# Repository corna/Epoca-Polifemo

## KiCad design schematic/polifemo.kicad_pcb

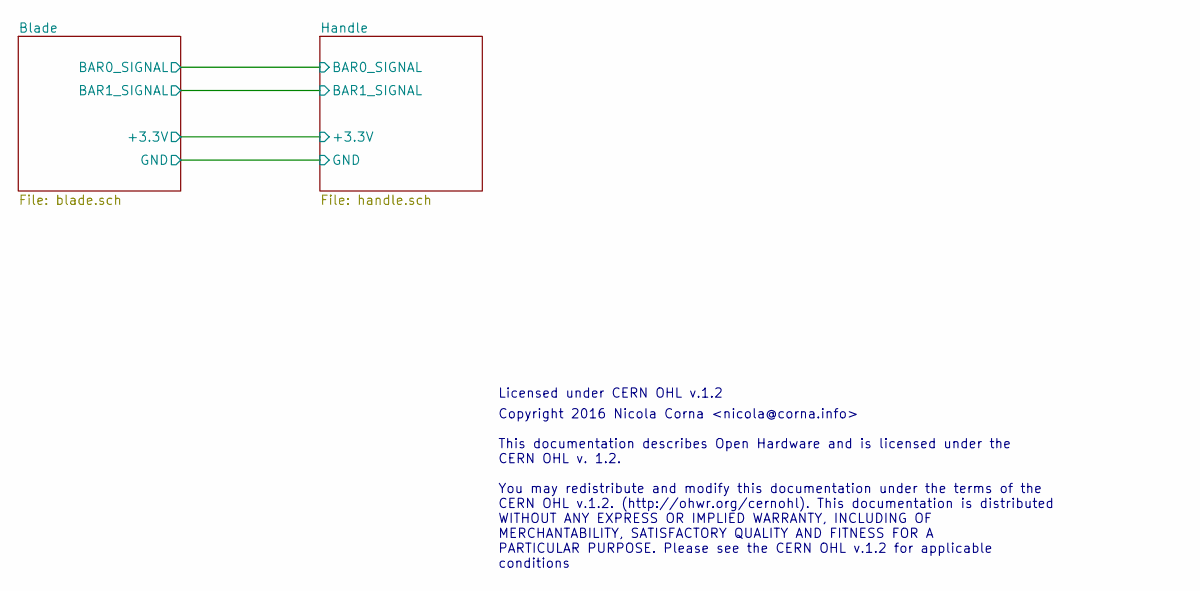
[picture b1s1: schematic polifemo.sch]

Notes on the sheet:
Copyright 2016 Nicola Corna <nicola@corna.info> This documentation describes Open Hardware and is licensed under the CERN OHL v. 1.2. You may redistribute and modify this documentation under the terms of the CERN OHL v.1.2. (http://ohwr.org/cernohl). This documentation is distributed WITHOUT ANY EX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
Licensed under CERN OHL v.1.2

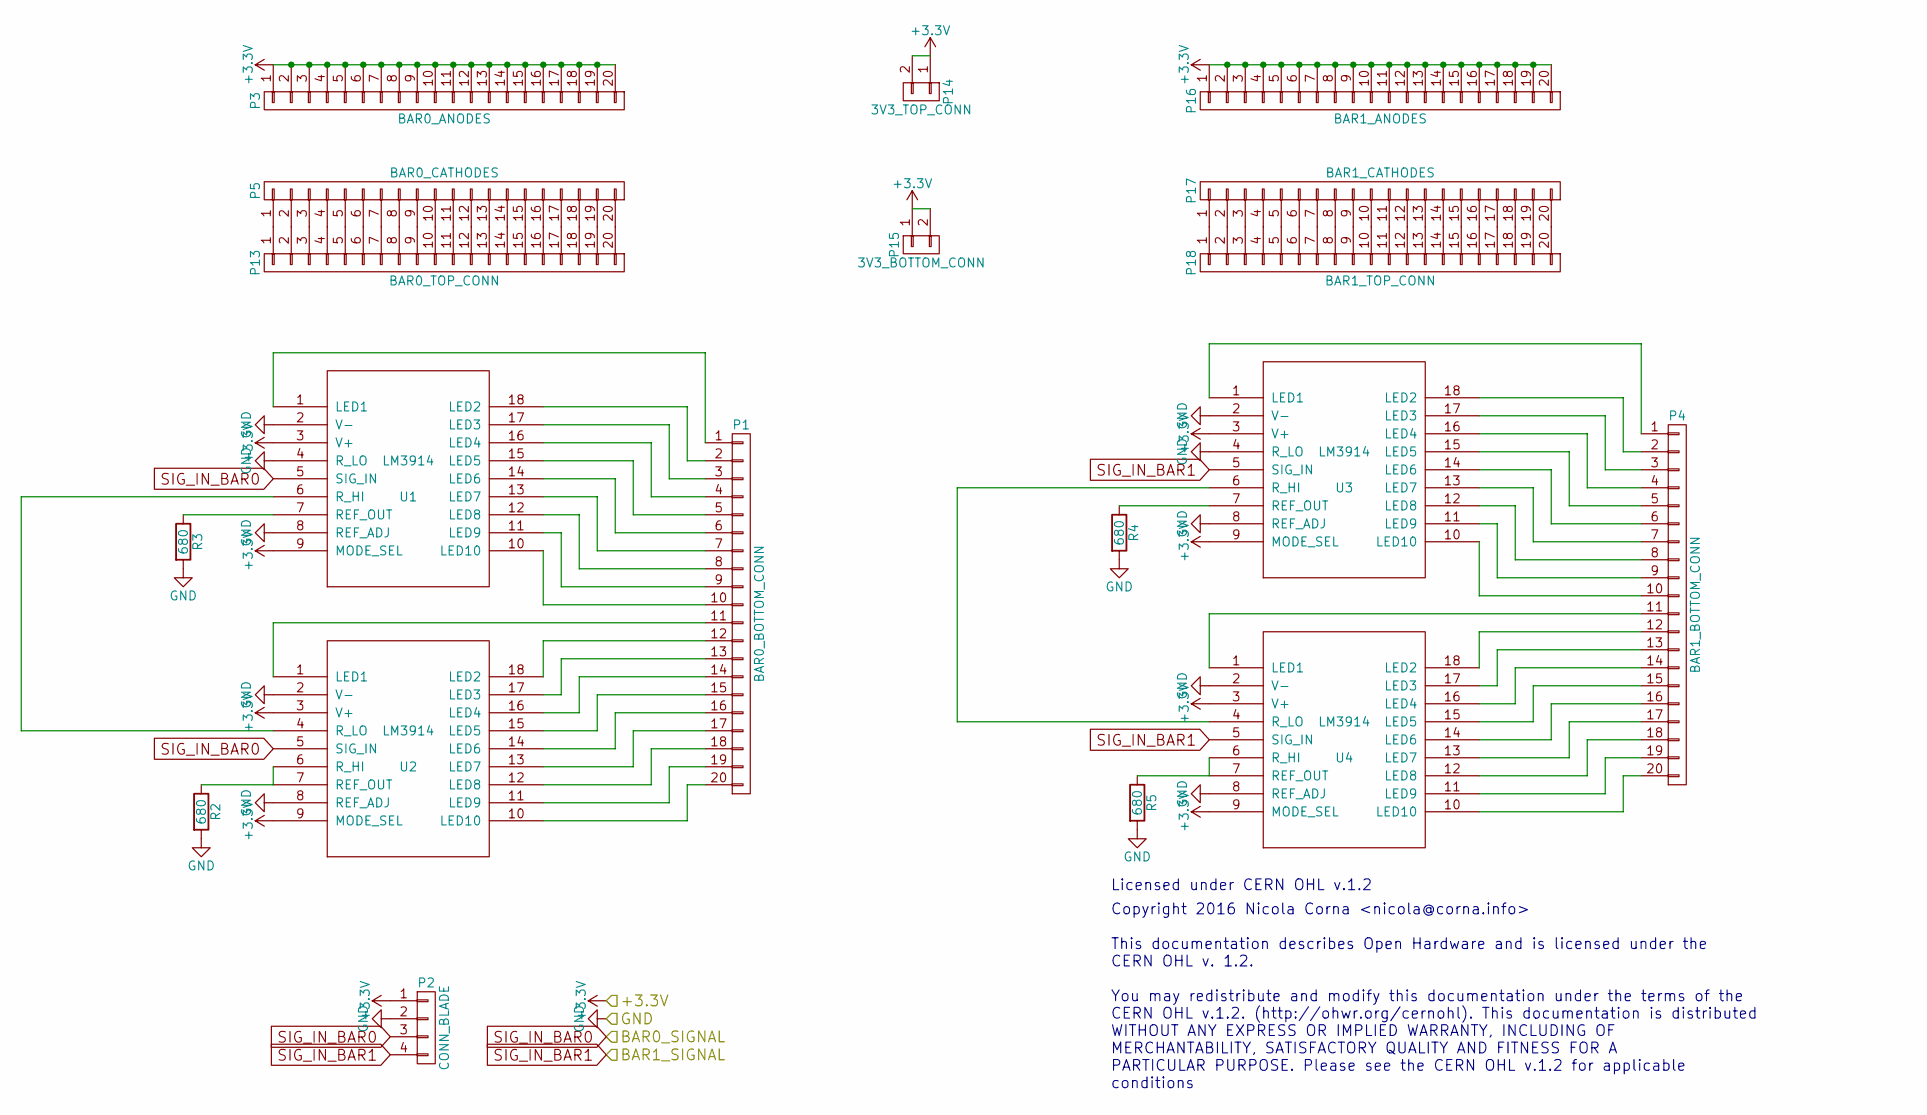
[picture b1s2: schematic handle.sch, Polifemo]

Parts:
P1: BAR0_BOTTOM_CONN; Pin_Header_Straight_1x20
P2: CONN_BLADE; Socket_Strip_Straight_1x04
P3: BAR0_ANODES; Socket_Strip_Straight_1x20
P4: BAR1_BOTTOM_CONN; Pin_Header_Straight_1x20
P5: BAR0_CATHODES; Socket_Strip_Straight_1x20
P13: BAR0_TOP_CONN; Socket_Strip_Straight_1x20
P14: 3V3_TOP_CONN; Socket_Strip_Straight_1x02
P15: 3V3_BOTTOM_CONN; Pin_Header_Straight_1x02
P16: BAR1_ANODES; Socket_Strip_Straight_1x20
P17: BAR1_CATHODES; Socket_Strip_Straight_1x20
P18: BAR1_TOP_CONN; Socket_Strip_Straight_1x20
R2, R3, R4, R5: 680; R_1206
U1, U2, U3, U4: LM3914; DIP-18_W7.62mm

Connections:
+3V3: P2.1, P3.1, P3.2, P3.3, P3.4, P3.5, P3.6, P3.7, P3.8, P3.9, P3.10, P3.11, P3.12, P3.13, P3.14, P3.15, P3.16, P3.17, P3.18, P3.19, P3.20, P14.1, P14.2, P15.1, P15.2, P16.1, P16.2, P16.3, P16.4, P16.5, P16.6, P16.7, P16.8, P16.9, P16.10, P16.11, P16.12, P16.13, P16.14, P16.15, P16.16, P16.17, P16.18, P16.19, P16.20, U1.3 (V+), U1.9 (MODE_SEL), U2.3 (V+), U2.9 (MODE_SEL), U3.3 (V+), U3.9 (MODE_SEL), U4.3 (V+), U4.9 (MODE_SEL); also elsewhere on the board
GND: P2.2, R2.2, R3.2, R4.2, R5.2, U1.2 (V-), U1.4 (R_LO), U1.8 (REF_ADJ), U2.2 (V-), U2.8 (REF_ADJ), U3.2 (V-), U3.4 (R_LO), U3.8 (REF_ADJ), U4.2 (V-), U4.8 (REF_ADJ); also elsewhere on the board
unnamed: P1.1, U1.1 (LED1)
unnamed: P1.2, U1.18 (LED2)
unnamed: P1.3, U1.17 (LED3)
unnamed: P1.4, U1.16 (LED4)
unnamed: P1.5, U1.15 (LED5)
unnamed: P1.6, U1.14 (LED6)
unnamed: P1.7, U1.13 (LED7)
unnamed: P1.8, U1.12 (LED8)
unnamed: P1.9, U1.11 (LED9)
unnamed: P1.10, U1.10 (LED10)
unnamed: P1.11, U2.1 (LED1)
unnamed: P1.12, U2.18 (LED2)
unnamed: P1.13, U2.17 (LED3)
unnamed: P1.14, U2.16 (LED4)
unnamed: P1.15, U2.15 (LED5)
unnamed: P1.16, U2.14 (LED6)
unnamed: P1.17, U2.13 (LED7)
unnamed: P1.18, U2.12 (LED8)
unnamed: P1.19, U2.11 (LED9)
unnamed: P1.20, U2.10 (LED10)
unnamed: P4.1, U3.1 (LED1)
unnamed: P4.2, U3.18 (LED2)
unnamed: P4.3, U3.17 (LED3)
unnamed: P4.4, U3.16 (LED4)
unnamed: P4.5, U3.15 (LED5)
unnamed: P4.6, U3.14 (LED6)
unnamed: P4.7, U3.13 (LED7)
unnamed: P4.8, U3.12 (LED8)
unnamed: P4.9, U3.11 (LED9)
unnamed: P4.10, U3.10 (LED10)
unnamed: P4.11, U4.1 (LED1)
unnamed: P4.12, U4.18 (LED2)
unnamed: P4.13, U4.17 (LED3)
unnamed: P4.14, U4.16 (LED4)
unnamed: P4.15, U4.15 (LED5)
unnamed: P4.16, U4.14 (LED6)
unnamed: P4.17, U4.13 (LED7)
unnamed: P4.18, U4.12 (LED8)
unnamed: P4.19, U4.11 (LED9)
unnamed: P4.20, U4.10 (LED10)
unnamed: P5.1, P13.1
unnamed: P5.2, P13.2
unnamed: P5.3, P13.3
unnamed: P5.4, P13.4
unnamed: P5.5, P13.5
unnamed: P5.6, P13.6
unnamed: P5.7, P13.7
unnamed: P5.8, P13.8
unnamed: P5.9, P13.9
unnamed: P5.10, P13.10
unnamed: P5.11, P13.11
unnamed: P5.12, P13.12
unnamed: P5.13, P13.13
unnamed: P5.14, P13.14
unnamed: P5.15, P13.15
unnamed: P5.16, P13.16
unnamed: P5.17, P13.17
unnamed: P5.18, P13.18
unnamed: P5.19, P13.19
unnamed: P5.20, P13.20
unnamed: P17.1, P18.1
unnamed: P17.2, P18.2
unnamed: P17.3, P18.3
unnamed: P17.4, P18.4
unnamed: P17.5, P18.5
unnamed: P17.6, P18.6
unnamed: P17.7, P18.7
unnamed: P17.8, P18.8
unnamed: P17.9, P18.9
unnamed: P17.10, P18.10
unnamed: P17.11, P18.11
unnamed: P17.12, P18.12
unnamed: P17.13, P18.13
unnamed: P17.14, P18.14
unnamed: P17.15, P18.15
unnamed: P17.16, P18.16
unnamed: P17.17, P18.17
unnamed: P17.18, P18.18
unnamed: P17.19, P18.19
unnamed: P17.20, P18.20
unnamed: R2.1, U2.6 (R_HI), U2.7 (REF_OUT)
unnamed: R3.1, U1.7 (REF_OUT)
unnamed: R4.1, U3.7 (REF_OUT)
unnamed: R5.1, U4.6 (R_HI), U4.7 (REF_OUT)
unnamed: U1.6 (R_HI), U2.4 (R_LO)
unnamed: U3.6 (R_HI), U4.4 (R_LO)
SIG_IN_BAR0: P2.3, U1.5 (SIG_IN), U2.5 (SIG_IN); also elsewhere on the board
SIG_IN_BAR1: P2.4, U3.5 (SIG_IN), U4.5 (SIG_IN); also elsewhere on the board

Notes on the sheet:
Copyright 2016 Nicola Corna <nicola@corna.info> This documentation describes Open Hardware and is licensed under the CERN OHL v. 1.2. You may redistribute and modify this documentation under the terms of the CERN OHL v.1.2. (http://ohwr.org/cernohl). This documentation is distributed WITHOUT ANY EX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
Licensed under CERN OHL v.1.2

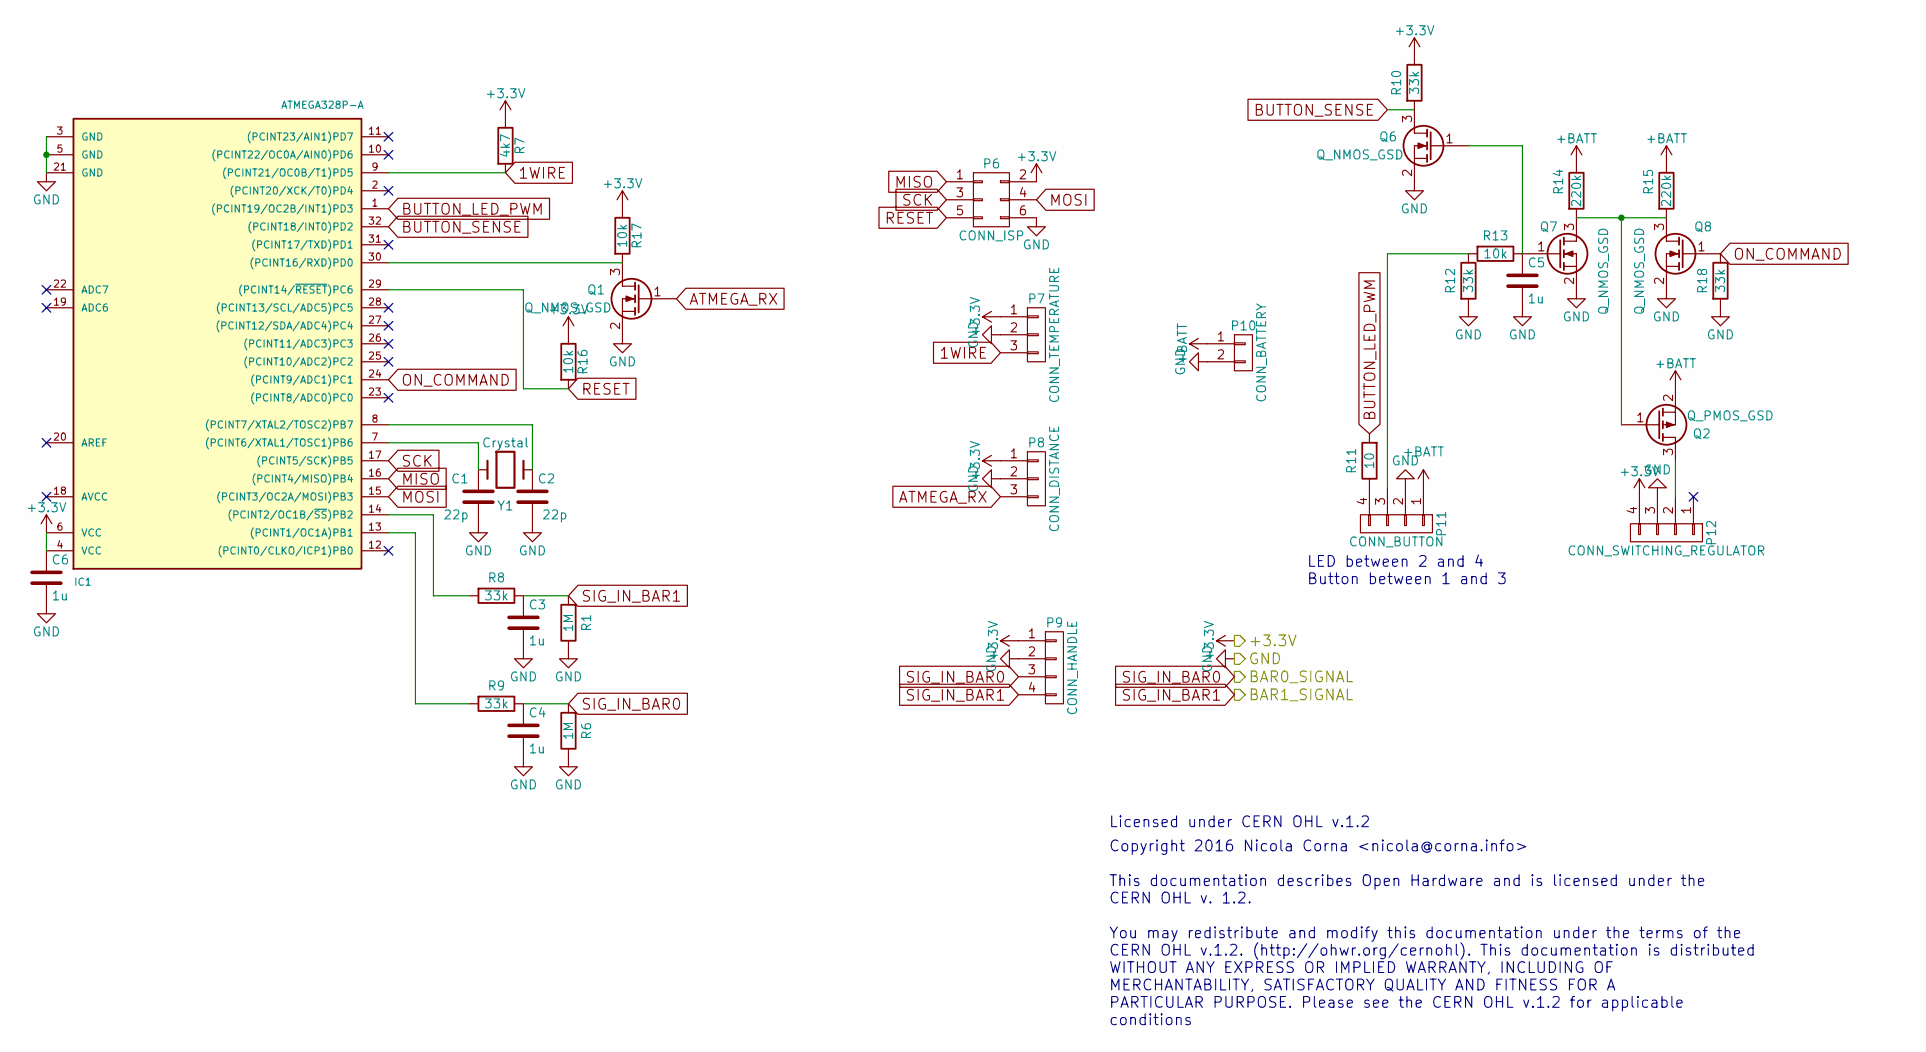
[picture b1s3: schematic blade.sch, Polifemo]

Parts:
C1, C2: 22p; C_1206
C3, C4, C5, C6: 1u; C_1206
IC1: ATMEGA328P-A; TQFP-32_7x7mm_Pitch0.8mm
P6: CONN_ISP; Pin_Header_Straight_2x03
P7: CONN_TEMPERATURE; Pin_Header_Straight_1x03
P8: CONN_DISTANCE; Pin_Header_Straight_1x03
P9: CONN_HANDLE; Socket_Strip_Straight_1x04
P10: CONN_BATTERY; Pin_Header_Straight_1x02
P11: CONN_BUTTON; Pin_Header_Straight_1x04
P12: CONN_SWITCHING_REGULATOR; Pin_Header_Straight_1x04
Q1, Q6, Q7, Q8: Q_NMOS_GSD; SOT-23
Q2: Q_PMOS_GSD; SOT-23
R1, R6: 1M; R_1206
R7: 4k7; R_1206
R8, R9, R10, R12, R18: 33k; R_1206
R11: 10; R_1206
R13, R16, R17: 10k; R_1206
R14, R15: 220k; R_1206
Y1: Crystal; Crystal_HC49-SD_SMD

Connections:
1WIRE: IC1.9 ((PCINT21/OC0B/T1)PD5), P7.3, R7.2
+3V3: C6.1, IC1.4 (VCC), IC1.6 (VCC), P6.2, P7.1, P8.1, P9.1, P12.4, R7.1, R10.1, R16.1, R17.1; also elsewhere on the board
+BATT: P10.1, P11.1, Q2.2 (S), R14.1, R15.1
ATMEGA_RX: P8.3, Q1.1 (G)
BUTTON_LED_PWM: IC1.1 ((PCINT19/OC2B/INT1)PD3), R11.2
BUTTON_SENSE: IC1.32 ((PCINT18/INT0)PD2), Q6.3 (D), R10.2
GND: C1.1, C2.2, C3.2, C4.2, C5.2, C6.2, IC1.3 (GND), IC1.5 (GND), IC1.21 (GND), P6.6, P7.2, P8.2, P9.2, P10.2, P11.2, P12.3, Q1.2 (S), Q6.2 (S), Q7.2 (S), Q8.2 (S), R1.1, R6.1, R12.2, R18.2; also elsewhere on the board
MISO: IC1.16 ((PCINT4/MISO)PB4), P6.1
MOSI: IC1.15 ((PCINT3/OC2A/MOSI)PB3), P6.4
unnamed: C1.2, IC1.7 ((PCINT6/XTAL1/TOSC1)PB6), Y1.1
unnamed: C2.1, IC1.8 ((PCINT7/XTAL2/TOSC2)PB7), Y1.2
unnamed: C5.1, Q6.1 (G), Q7.1 (G), R13.1
unnamed: IC1.13 ((PCINT1/OC1A)PB1), R9.2
unnamed: IC1.14 ((PCINT2/OC1B/~SS~)PB2), R8.2
unnamed: IC1.30 ((PCINT16/RXD)PD0), Q1.3 (D), R17.2
unnamed: P11.3, R12.1, R13.2
unnamed: P11.4, R11.1
unnamed: P12.2, Q2.3 (D)
unnamed: Q2.1 (G), Q7.3 (D), Q8.3 (D), R14.2, R15.2
ON_COMMAND: IC1.24 ((PCINT9/ADC1)PC1), Q8.1 (G), R18.1
RESET: IC1.29 ((PCINT14/~RESET~)PC6), P6.5, R16.2
SCK: IC1.17 ((PCINT5/SCK)PB5), P6.3
SIG_IN_BAR0: C4.1, P9.3, R6.2, R9.1; also elsewhere on the board
SIG_IN_BAR1: C3.1, P9.4, R1.2, R8.1; also elsewhere on the board

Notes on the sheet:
LED between 2 and 4 Button between 1 and 3
Copyright 2016 Nicola Corna <nicola@corna.info> This documentation describes Open Hardware and is licensed under the CERN OHL v. 1.2. You may redistribute and modify this documentation under the terms of the CERN OHL v.1.2. (http://ohwr.org/cernohl). This documentation is distributed WITHOUT ANY EX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
Licensed under CERN OHL v.1.2

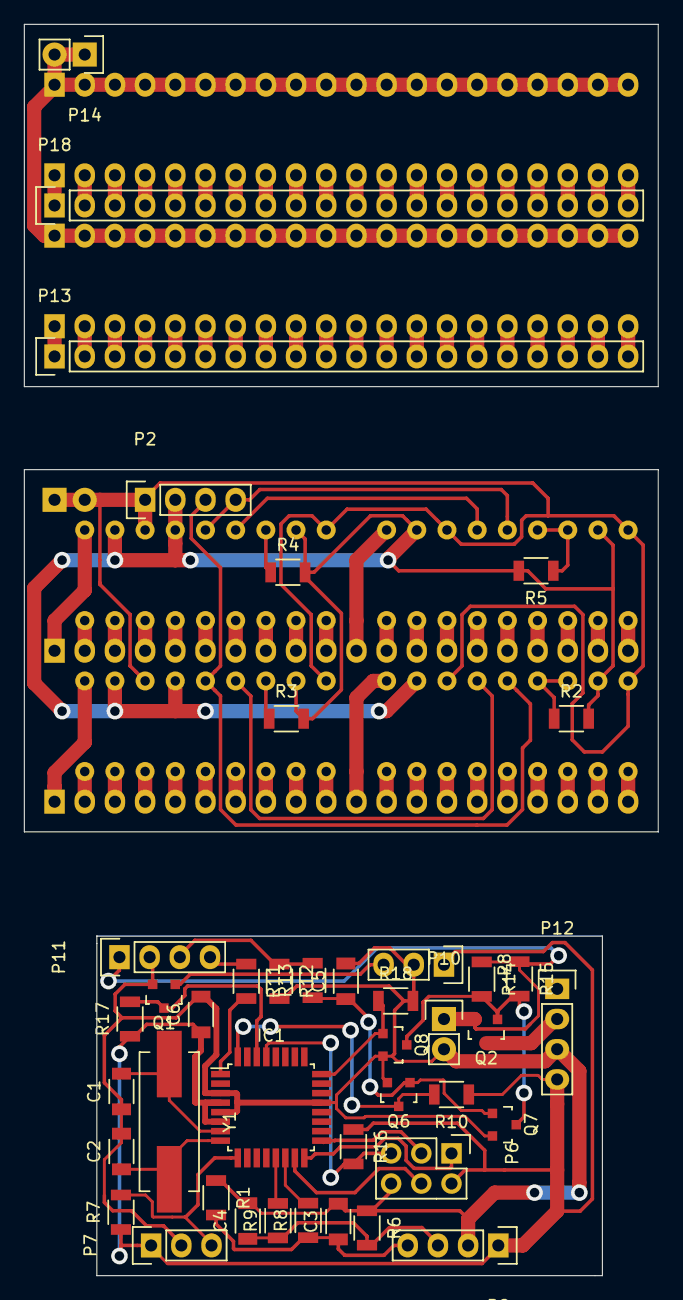
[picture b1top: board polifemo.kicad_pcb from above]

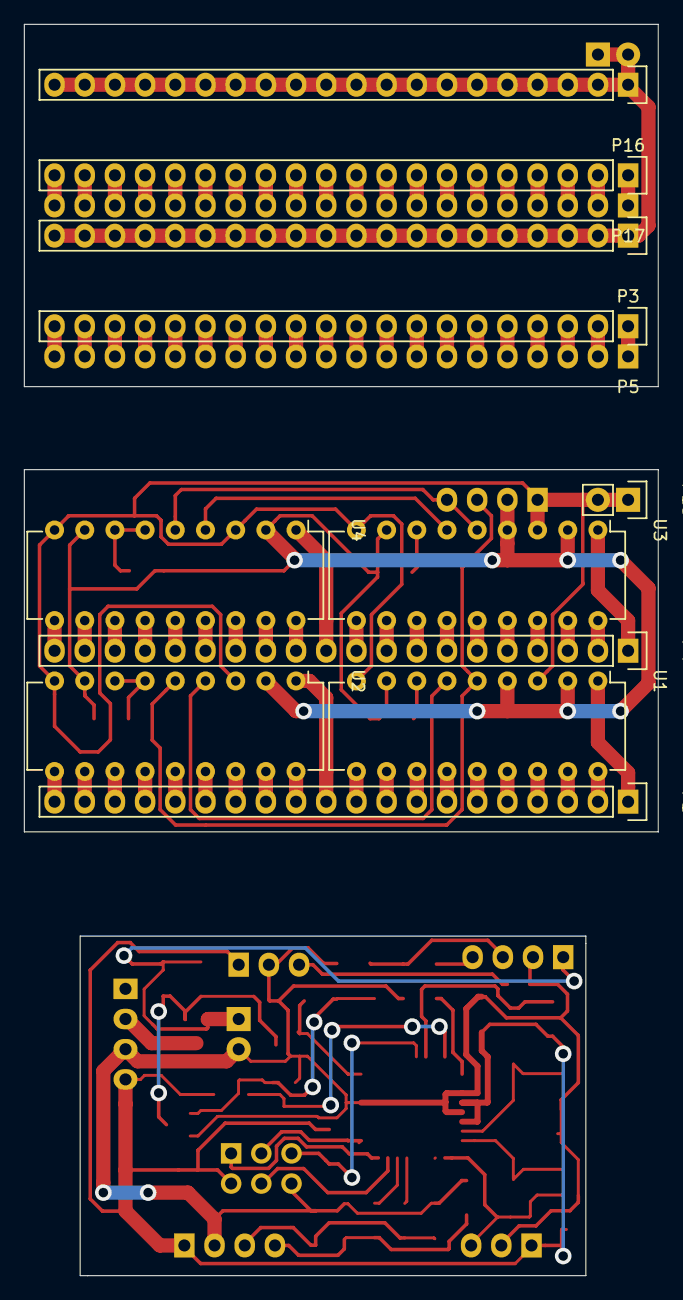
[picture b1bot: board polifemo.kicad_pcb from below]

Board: 2 copper layers, 53.3 x 105.3 mm, 53 parts (11 on the bottom side), 110 nets.

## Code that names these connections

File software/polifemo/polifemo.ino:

/*
 * Epoca Polifemo
 * Copyright (C) 2016 Nicola Corna <nicola@corna.info>
 *
 * This program is free software: you can redistribute it and/or modify
 * it under the terms of the GNU General Public License as published by
 * the Free Software Foundation, either version 3 of the License, or
 * (at your option) any later version.
 *
 * This program is distributed in the hope that it will be useful,
 * but WITHOUT ANY WARRANTY; without even the implied warranty of
 * MERCHANTABILITY or FITNESS FOR A PARTICULAR PURPOSE.  See the
 * GNU General Public License for more details.
 *
 * You should have received a copy of the GNU General Public License
 * along with this program.  If not, see <http://www.gnu.org/licenses/>.
 *
 */

#include <avr/sfr_defs.h>
#include <avr/wdt.h>
#include <stdint.h>

#include <TaskScheduler.h>
#include <OneWire.h>
#include <DallasTemperature.h>

#include "MedianFilter.h"
#include "MovingAverage.h"

const uint8_t onCommand = A1;   // PC1 (A1 = 15)
const uint8_t buttonLedPWM = 3; // PD3, OC2B
const uint8_t buttonSense = 2;  // PD2, INT0
const uint8_t sigBar0 = 9;      // PB1, OC1A
const uint8_t sigBar1 = 10;     // PB2, OC1B
const uint8_t ds18b20 = 5;      // PD5 (OC0B)

const unsigned long totalTime = 20000;
const uint16_t refreshPeriod = 120;

const uint8_t watchDogTimeout = WDTO_500MS; //Make sure that watchDogTimeout >> refreshPeriod

const uint16_t dimUpPeriod = 5;
const uint8_t dimUpStep = 2;    //The total dimUp time is dimUpPeriod * (255 / dimUpStep)

const uint16_t dimDownPeriod = 10;
const uint8_t dimDownStep = 2;  //The total dimDown time is dimDownPeriod * (255 / dimDownStep)

/*
const uint16_t distanceMin = 20;
const uint16_t distanceMax = 765;
*/

//30 cm per step
const uint16_t distanceMin = 20;
const uint16_t distanceMax = 600;

//2 °C per step
const int16_t temperatureMin = -3 * 128;
const int16_t temperatureMax = 35 * 128;

//The maximum input value for the LED bars is 1.25V: we have to scale the maximum PWM in order to match it
const uint8_t sigBarMaxPWM = 115;

int16_t ledBrightness = 0;
bool buttonPressed = false;

OneWire oneWire(ds18b20);
DallasTemperature temperatureBus(&oneWire);
DeviceAddress temperatureAddress;

int16_t temperature = 20 * 128;  // 1/128 °C
uint16_t distance = 20;   // cm

MedianFilter<uint16_t, 3> distanceMedian(0xFFFF, distance);
MovingAverage<uint16_t, 5> distanceAverage(distance);

String rawRx = "";

//Forward declarations
void powerButtonPressed();
void displayData();
void updateAndDisplayData();
void dimUp();
void dimDown();
void powerOffSequence();

Task updateAndDisplayDataTask(refreshPeriod, TASK_FOREVER, &updateAndDisplayData);
Task dimUpTask(dimUpPeriod, TASK_FOREVER, &dimUp);
Task dimDownTask(dimDownPeriod, TASK_FOREVER, &dimDown);
Task powerOffSequenceTask(totalTime, TASK_ONCE, &powerOffSequence);

Scheduler runner;

//Disable the watchdog as soon as possible (we don't want the watchdog during the initialization phase)
//see http://www.nongnu.org/avr-libc/user-manual/group__avr__watchdog.html
void get_mcusr(void) __attribute__((naked)) __attribute__((section(".init3")));
void get_mcusr(void)
{
  MCUSR = 0;
  wdt_disable();
}

void setup() {
  //Set the direction and the default value of all the pins
  pinMode(onCommand, OUTPUT);
  digitalWrite(onCommand, HIGH);

  pinMode(buttonLedPWM, OUTPUT);
  analogWrite(buttonLedPWM, ledBrightness);

  pinMode(buttonSense, INPUT);
  //Not optimal: if the user keeps the button pressed the interrupt is fired only once (but who cares??)
  attachInterrupt(digitalPinToInterrupt(buttonSense), powerButtonPressed, CHANGE);

  pinMode(sigBar0, OUTPUT);
  pinMode(sigBar1, OUTPUT);

  displayData();

  //We're throwing the sigBarN outputs in a 1st order LPF, therefore the higher the frequency of the PWM, the more stable the response
  //Here's we're setting the prescaler equal to 1 and the Fast-PWM mode (PWM frequency = 43.2 kHz)
  //This interferes with the Servo library
  TCCR1B |= _BV(CS10) | _BV(WGM12);
  TCCR1B &= ~( _BV(CS11) | _BV(CS12) );

  Serial.begin(9600);

  temperatureBus.begin();
  if (temperatureBus.getAddress(temperatureAddress, 0))
  {
    temperatureBus.setWaitForConversion(false);
    temperatureBus.setResolution(9);
    temperatureBus.requestTemperatures();
  }

  pinMode(LED_BUILTIN, OUTPUT);
  delay(100); //Now both the measurements should be ready

  runner.addTask(updateAndDisplayDataTask);
  runner.addTask(dimUpTask);
  runner.addTask(dimDownTask);
  runner.addTask(powerOffSequenceTask);

  updateAndDisplayDataTask.enableDelayed();
  dimUpTask.enableDelayed();
  powerOffSequenceTask.enableDelayed();
  
  wdt_reset();
  wdt_enable(watchDogTimeout);  //Enable the watchdog; see dimDown
}

void loop() {
  runner.execute();

  if (buttonPressed) {
    buttonPressed = false;
    powerOffSequenceTask.restartDelayed();  //Restart the poweroff timer
    dimDownTask.disable();                  //Remove an eventual dimDown
  
    if (ledBrightness != 255)
      dimUpTask.enableDelayed();  //Increase the LED's brightness if they're not at 100%
    }
}

void powerButtonPressed() {
  buttonPressed = true;
}

void updateAndDisplayData() {
  static String rawRx;
  int8_t start;
  int8_t end;
  char buffer[65];
  int16_t rawTemperature;
  
  wdt_reset();

  //Temperature
  rawTemperature = temperatureBus.getTemp(temperatureAddress);
  if (rawTemperature > DEVICE_DISCONNECTED_RAW)
    temperature = constrain(rawTemperature, temperatureMin, temperatureMax);

  temperatureBus.requestTemperaturesByAddress(temperatureAddress);
  
  //Distance
  end = Serial.available();
  Serial.readBytes(buffer, end);
  buffer[end] = '\0';

  rawRx += buffer;
  end = rawRx.lastIndexOf('\r');
  
  if (end > 0) {
    start = rawRx.lastIndexOf('R', end);

    if (start >= 0) {
      uint16_t unfilteredDistance = rawRx.substring(start + 1, end).toInt();
      
      if (unfilteredDistance != 0) {
        distance = distanceAverage.filter(distanceMedian.filter(constrain(unfilteredDistance, distanceMin, distanceMax)));
      }
      
      rawRx.remove(0, end + 1); //Throw away older data
    }
  }

  displayData();

  wdt_reset();
}

void displayData() {
  static const uint8_t sigBarStep = sigBarMaxPWM / 19;
  static const uint8_t sigBarStep_2 = sigBarStep / 2;

  uint8_t value;

  //Find the maximum PWM value, a combination of ledBrightness (0->255) and sigBarMaxPWM(0->255)
  //For an explaination of that "+ 1" see this link http://forum.arduino.cc/index.php/topic,46546.0.html
  const uint8_t maxPWM = map(ledBrightness, 0, 255 + 1, 0, sigBarMaxPWM + 1);

  //Then map the distance (distanceMin->distanceMax) to the new PWM range(0->maxPWM)
  value = map(distance, distanceMin, distanceMax + 1, 0, maxPWM + 1);

  //Then approximate the final value to one of the 20 steps
  value = (value + sigBarStep_2) / sigBarStep * sigBarStep;
  analogWrite(sigBar1, value);

  value =  map(temperature, temperatureMin, temperatureMax + 1, 0, maxPWM + 1);
  value = (value + sigBarStep_2) / sigBarStep * sigBarStep;
  analogWrite(sigBar0, value);
}

void dimUp() {
  ledBrightness = constrain(ledBrightness + dimUpStep, 0, 255);
  analogWrite(buttonLedPWM, ledBrightness);
  displayData();

  if (ledBrightness == 255) //Maximum brightness reached
    dimUpTask.disable();
}

void dimDown() {
  ledBrightness = constrain(ledBrightness - dimDownStep, 0, 255);
  analogWrite(buttonLedPWM, ledBrightness);
  displayData();

  if (ledBrightness == 0) { //Minimum brightness reached
    digitalWrite(onCommand, LOW); //Power off everything

    wdt_reset();
    while(true) {    
      //Force a watchdog timeout if the AVR is still on after watchDogTimeout
      //This is to prevent dead-lock situations that can occur if the user press the button exactly
      //after digitalWrite(onCommand, LOW), as the capacitors keep the AVR powered for a while
    }
  }
}

void powerOffSequence() {
  dimDownTask.enableDelayed();  //Start the "dimDown" countdown
}

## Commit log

2016-04-04 Working release
2016-07-15 Minor filter fix
